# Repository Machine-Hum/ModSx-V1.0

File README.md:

ModSx-V1.0
==========

Please note this project has been discontined, see ModSx-V2.0.

https://github.com/Machine-Hum/ModSx-V2.0

The ModSx isa cross between the Arduino and a modular synths. 
Each module is a PCB that stacks on top of other modules. DC lines and signaling lines flow up 
the stack, these provide power, analog data and digital data to all the connected modules. Right 
angle headers are used for analog signal routing where needed. Wires are used to connect channels. 
The purpose is to reduce cost of modular synths by removing the mechanical aspect. Boards will use 
through hole components where possible, to enable the user to solder their own modules. The entire 
project will increase the accessibility of high quality audio components while increasing the 
customizability, yet keeping the complexity low to the end user.

PowerBoard
--------
/PowerBoard.JPG)

The power board, takes DC Vin from a large right angle screw terminal or power jack and conditions it to +3.3V, +5V, +0.5(Vin) and -0.5(Vin). Vin typical would be +24V, giving a +12V and -12V. 

AuxBreak
--------
/AuxBreak.JPG)

The Aux breakout, breaks out standard 3.5mm auxiliary cables into pins. The pins serve as interconnects for signal routing.

Proto Board
--------
/ProtoBoard.JPG)

The protoboard is for prototyping future circuits, basic hole patterns on the top for soldering.

8Bit LFO / VCO
--------
Low frequency oscillator (1-20Hz) sin, triangle or square wave. Takes in 0-10V into input pin, frequency is scaled linearly throughout the range. Waveform is selected from 0/10V discrete signal on pins.
Ideally the same board will be used for 2Khz-20Khz VCO, but I’m worried that the uC will not be able to keep up. VCO might be square wave only.

Power Amp
--------
/PowerAmp.JPG)

The power amp is a 4 channel low wattage amplifier based off the LM386. 

-Walker

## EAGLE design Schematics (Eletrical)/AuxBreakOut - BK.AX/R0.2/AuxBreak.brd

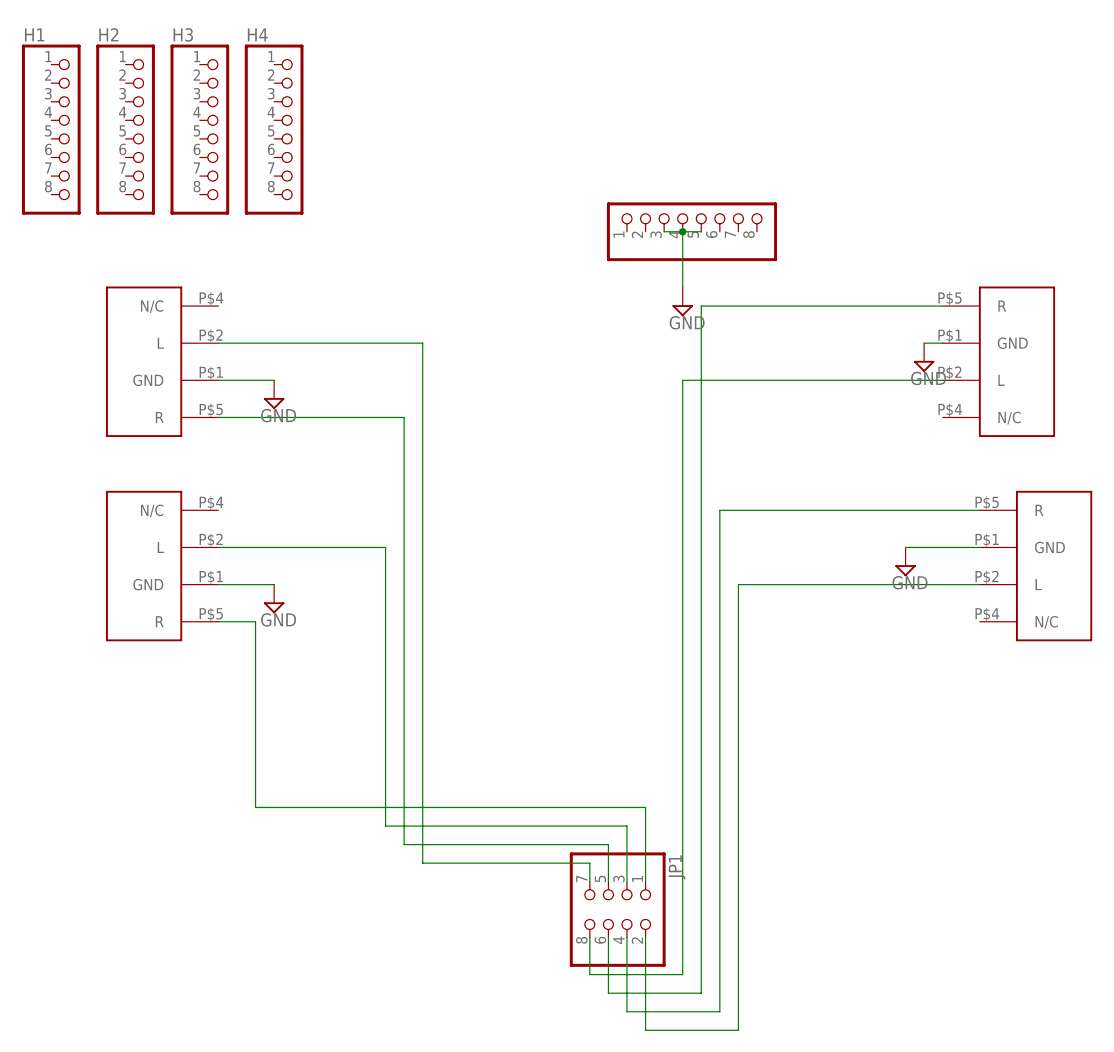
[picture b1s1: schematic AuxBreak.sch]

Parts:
H1, H2, H3, H4, H5: PINHD-1X8; 1X08
JP1: PINHD-2X4/90; 2X04/90
U$1, U$3, U$4, U$5: 161-3509-E

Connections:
GND: H5.3, H5.4, H5.5, U$1.P$1 (GND), U$3.P$1 (GND), U$4.P$1 (GND), U$5.P$1 (GND)
unnamed: JP1.7, U$5.P$2 (L)
unnamed: JP1.5, U$5.P$5 (R)
unnamed: JP1.3, U$4.P$2 (L)
unnamed: JP1.1, U$4.P$5 (R)
unnamed: JP1.8, U$1.P$2 (L)
unnamed: JP1.6, U$1.P$5 (R)
unnamed: JP1.4, U$3.P$5 (R)
unnamed: JP1.2, U$3.P$2 (L)

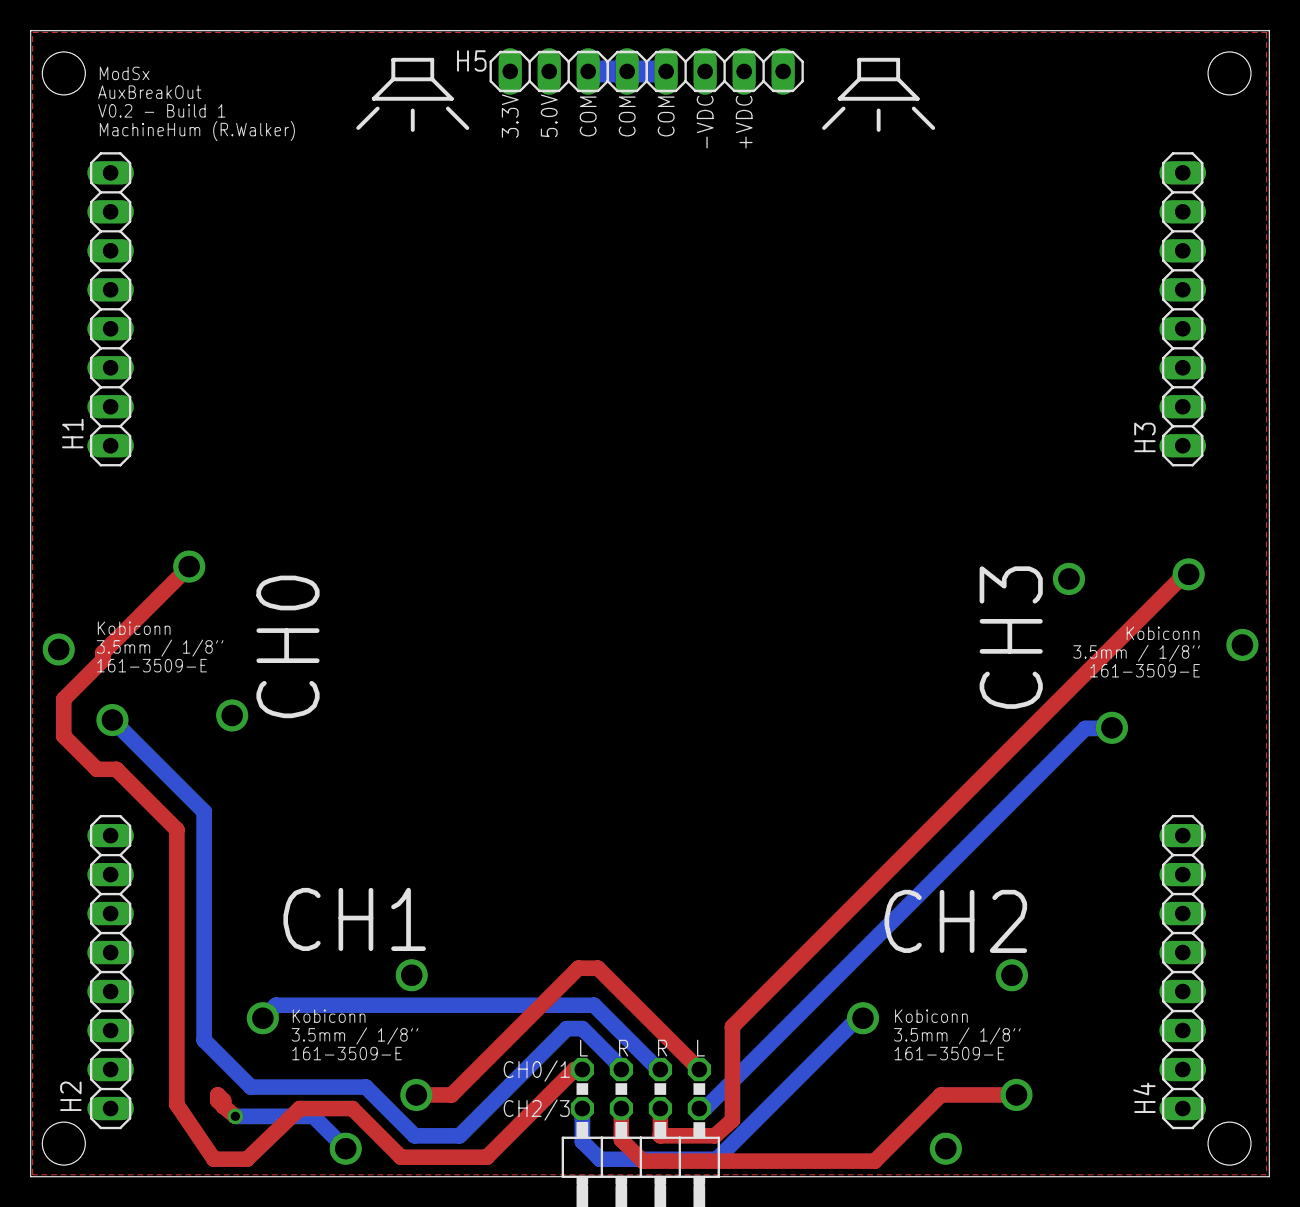
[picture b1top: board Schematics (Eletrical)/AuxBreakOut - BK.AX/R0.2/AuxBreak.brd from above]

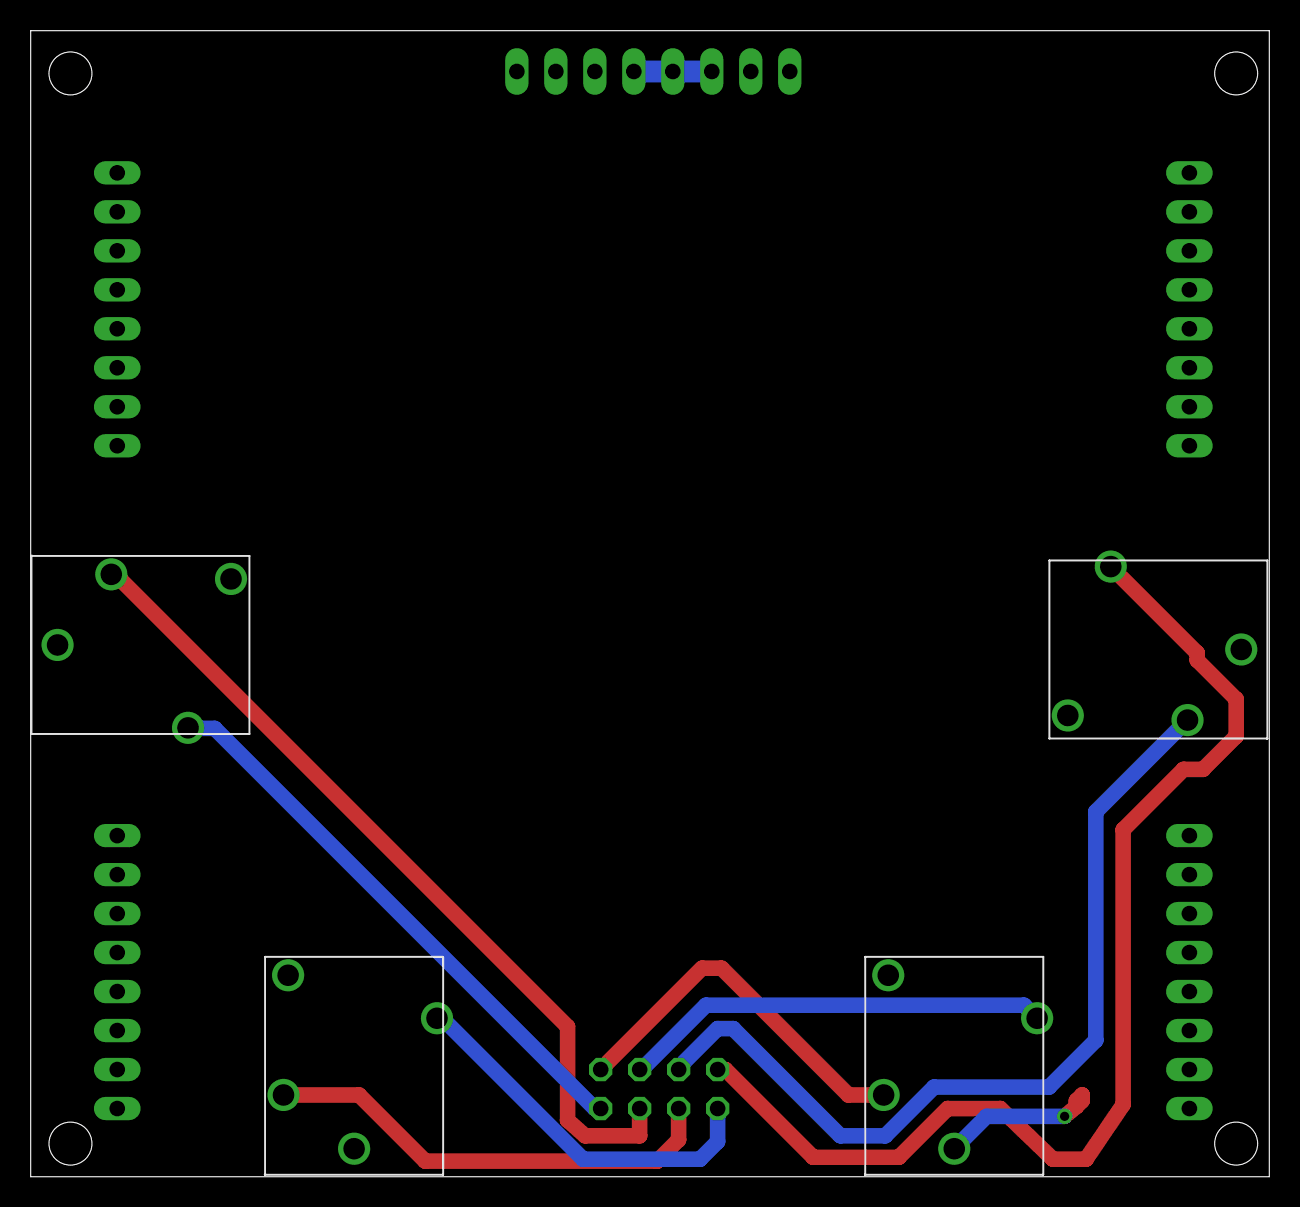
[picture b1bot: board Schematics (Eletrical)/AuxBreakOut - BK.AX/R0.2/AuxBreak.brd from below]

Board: 2 copper layers, 80.7 x 74.7 mm, 10 parts (4 on the bottom side), 9 nets.

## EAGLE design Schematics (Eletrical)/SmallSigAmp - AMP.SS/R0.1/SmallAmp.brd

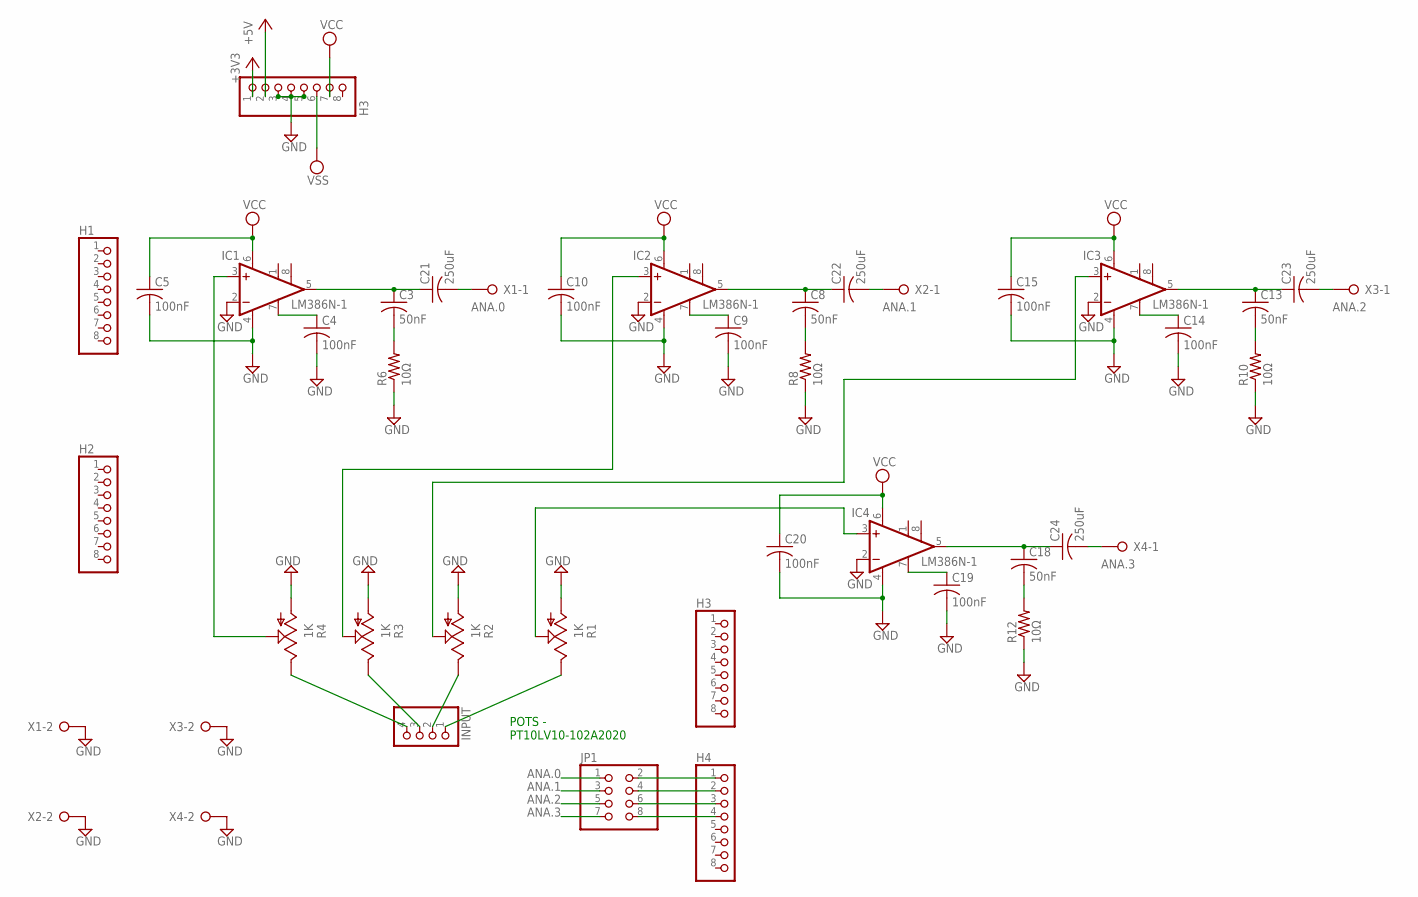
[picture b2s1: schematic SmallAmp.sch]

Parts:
C3, C8, C13, C18: 50nF; C075-032X103
C4, C5, C9, C10, C14, C15, C19, C20: 100nF; C075-032X103
C21, C22, C23, C24: 250uF; C025-050X050
H1, H2, H3, H4: PINHD-1X8; 1X08
IC1, IC2, IC3, IC4: LM386N-1; DIL08
INPUT: PINHD-1X4/90; 1X04/90
JP1: PINHD-2X4; 2X04
JP3: H3; 1X08
R1, R2, R3, R4: 1K; PT-10
R6, R8, R10, R12: 10Ω; 0204/7
X1, X2, X3, X4: W237-02P; W237-132

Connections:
+3V3: JP3.1
+5V: JP3.2
ANA.0: C21.2, JP1.1, X1.1
ANA.1: C22.2, JP1.3, X2.1
ANA.2: C23.2, JP1.5, X3.1
ANA.3: C24.2, JP1.7, X4.1
GND: C4.2, C5.2, C9.2, C10.2, C14.2, C15.2, C19.2, C20.2, IC1.2 (-IN), IC1.4 (GND), IC2.2 (-IN), IC2.4 (GND), IC3.2 (-IN), IC3.4 (GND), IC4.2 (-IN), IC4.4 (GND), JP3.3, JP3.4, JP3.5, R1.A, R2.A, R3.A, R4.A, R6.1, R8.1, R10.1, R12.1, X1.2, X2.2, X3.2, X4.2
unnamed: INPUT.1, R1.E
unnamed: INPUT.2, R2.E
unnamed: INPUT.3, R3.E
unnamed: INPUT.4, R4.E
unnamed: IC1.3 (+IN), R4.S
unnamed: H4.1, JP1.2
unnamed: C3.1, C21.1, IC1.5 (OUT)
unnamed: H4.2, JP1.4
unnamed: C3.2, R6.2
unnamed: C4.1, IC1.7 (BYPASS)
unnamed: IC2.3 (+IN), R3.S
unnamed: C8.1, C22.1, IC2.5 (OUT)
unnamed: H4.3, JP1.6
unnamed: C8.2, R8.2
unnamed: H4.4, JP1.8
unnamed: C9.1, IC2.7 (BYPASS)
unnamed: IC3.3 (+IN), R2.S
unnamed: C13.1, C23.1, IC3.5 (OUT)
unnamed: C13.2, R10.2
unnamed: C14.1, IC3.7 (BYPASS)
unnamed: IC4.3 (+IN), R1.S
unnamed: C18.1, C24.1, IC4.5 (OUT)
unnamed: C18.2, R12.2
unnamed: C19.1, IC4.7 (BYPASS)
VCC: C5.1, C10.1, C15.1, C20.1, IC1.6 (VS), IC2.6 (VS), IC3.6 (VS), IC4.6 (VS), JP3.7
VSS: JP3.6

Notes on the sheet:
POTS - PT10LV10-102A2020
ANA.0
ANA.1
ANA.2
ANA.3

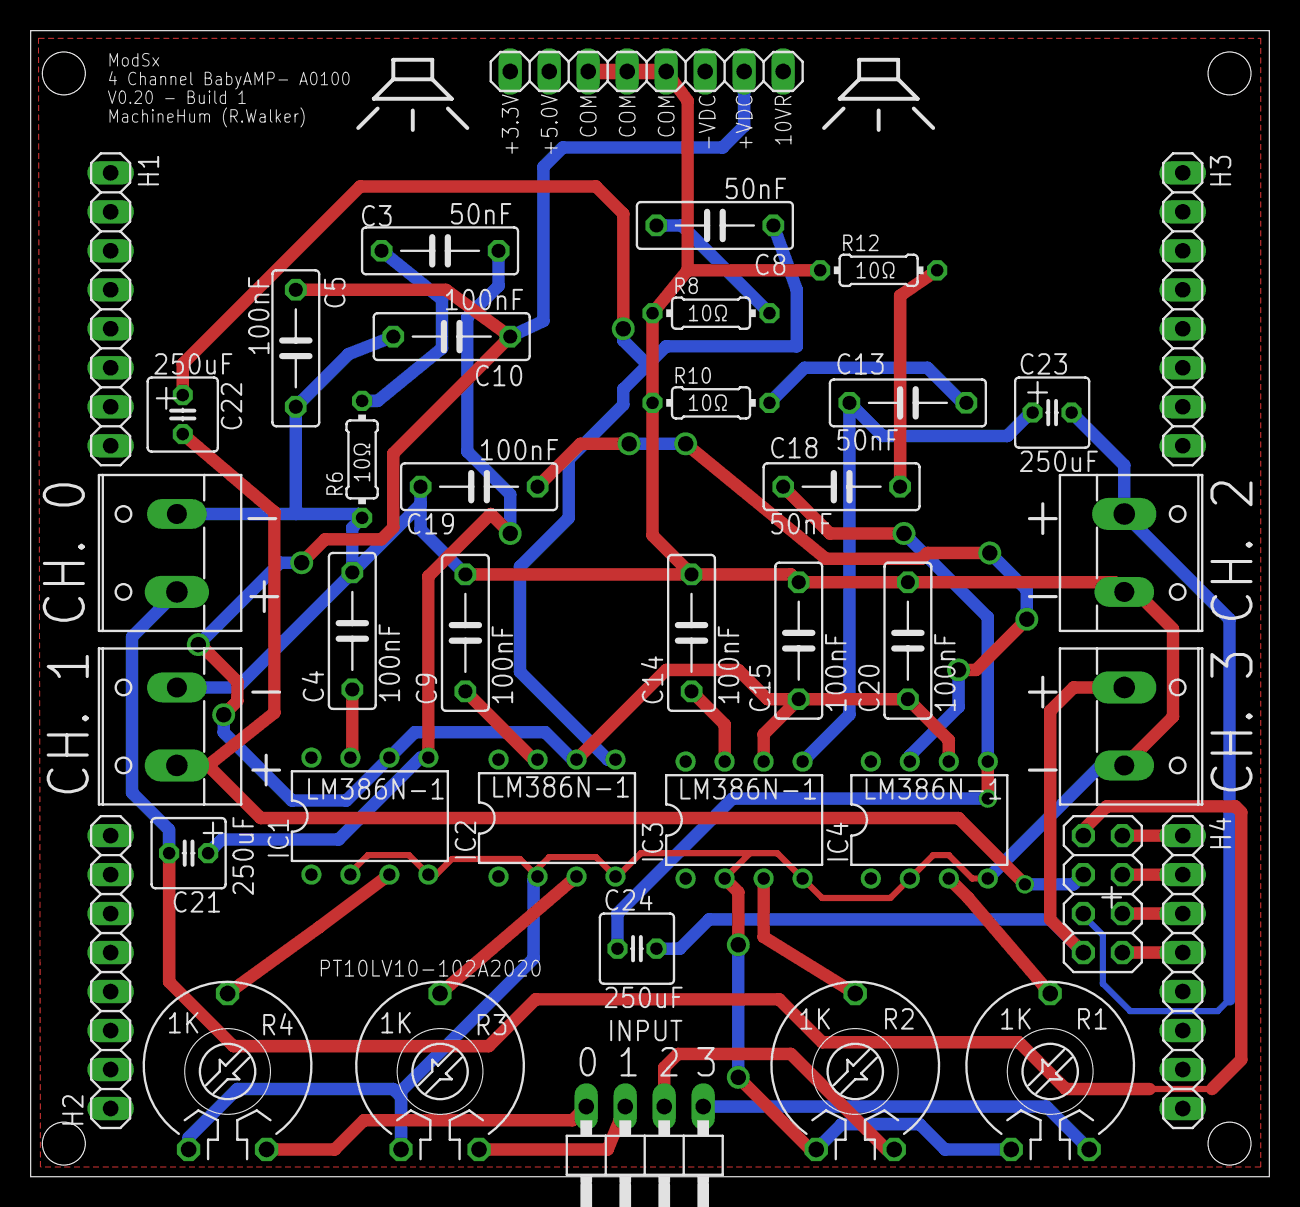
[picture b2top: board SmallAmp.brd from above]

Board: 2 copper layers, 80.7 x 74.7 mm, 39 parts (0 on the bottom side), 30 nets.

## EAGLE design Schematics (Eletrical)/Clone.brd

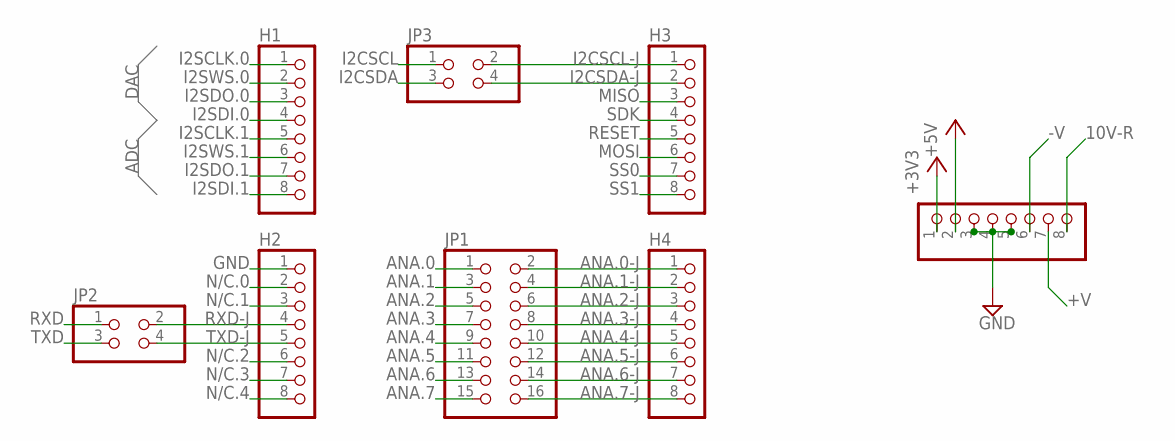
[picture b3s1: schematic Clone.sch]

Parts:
H1, H2, H3, H4, H5: PINHD-1X8; 1X08
JP1: PINHD-2X8; 2X08
JP2, JP3: PINHD-2X2; 2X02

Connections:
10V-R: H5.8
+3V3: H5.1
+5V: H5.2
+V: H5.7
-V: H5.6
ANA.0: JP1.1
ANA.0-J: H4.1, JP1.2
ANA.1: JP1.3
ANA.1-J: H4.2, JP1.4
ANA.2: JP1.5
ANA.2-J: H4.3, JP1.6
ANA.3: JP1.7
ANA.3-J: H4.4, JP1.8
ANA.4: JP1.9
ANA.4-J: H4.5, JP1.10
ANA.5: JP1.11
ANA.5-J: H4.6, JP1.12
ANA.6: JP1.13
ANA.6-J: H4.7, JP1.14
ANA.7: JP1.15
ANA.7-J: H4.8, JP1.16
GND: H2.1, H5.3, H5.4, H5.5
I2CSCL: JP3.1
I2CSCL-J: H3.1, JP3.2
I2CSDA: JP3.3
I2CSDA-J: H3.2, JP3.4
I2SCLK.0: H1.1
I2SCLK.1: H1.5
I2SDI.0: H1.4
I2SDI.1: H1.8
I2SDO.0: H1.3
I2SDO.1: H1.7
I2SWS.0: H1.2
I2SWS.1: H1.6
MISO: H3.3
MOSI: H3.6
N/C.0: H2.2
N/C.1: H2.3
N/C.2: H2.6
N/C.3: H2.7
N/C.4: H2.8
RESET: H3.5
RXD: JP2.1
RXD-J: H2.4, JP2.2
SCK: H3.4
SS0: H3.7
SS1: H3.8
TXD: JP2.3
TXD-J: H2.5, JP2.4

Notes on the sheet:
10V-R
I2SCLK.0
I2SWS.0
I2SDO.0
I2SDI.0
I2SCLK.1
I2SWS.1
I2SDO.1
I2SDI.1
GND
N/C.0
RXD-J
TXD-J
N/C.1
N/C.2
N/C.3
N/C.4
I2CSCL
I2CSDA
MISO
SDK
RESET
MOSI
SS0
SS1
ANA.0-J
ANA.1-J
ANA.2-J
ANA.3-J
ANA.4-J
ANA.5-J
ANA.6-J
ANA.7-J
ANA.0
ANA.1
ANA.2
ANA.3
ANA.4
ANA.5
ANA.6

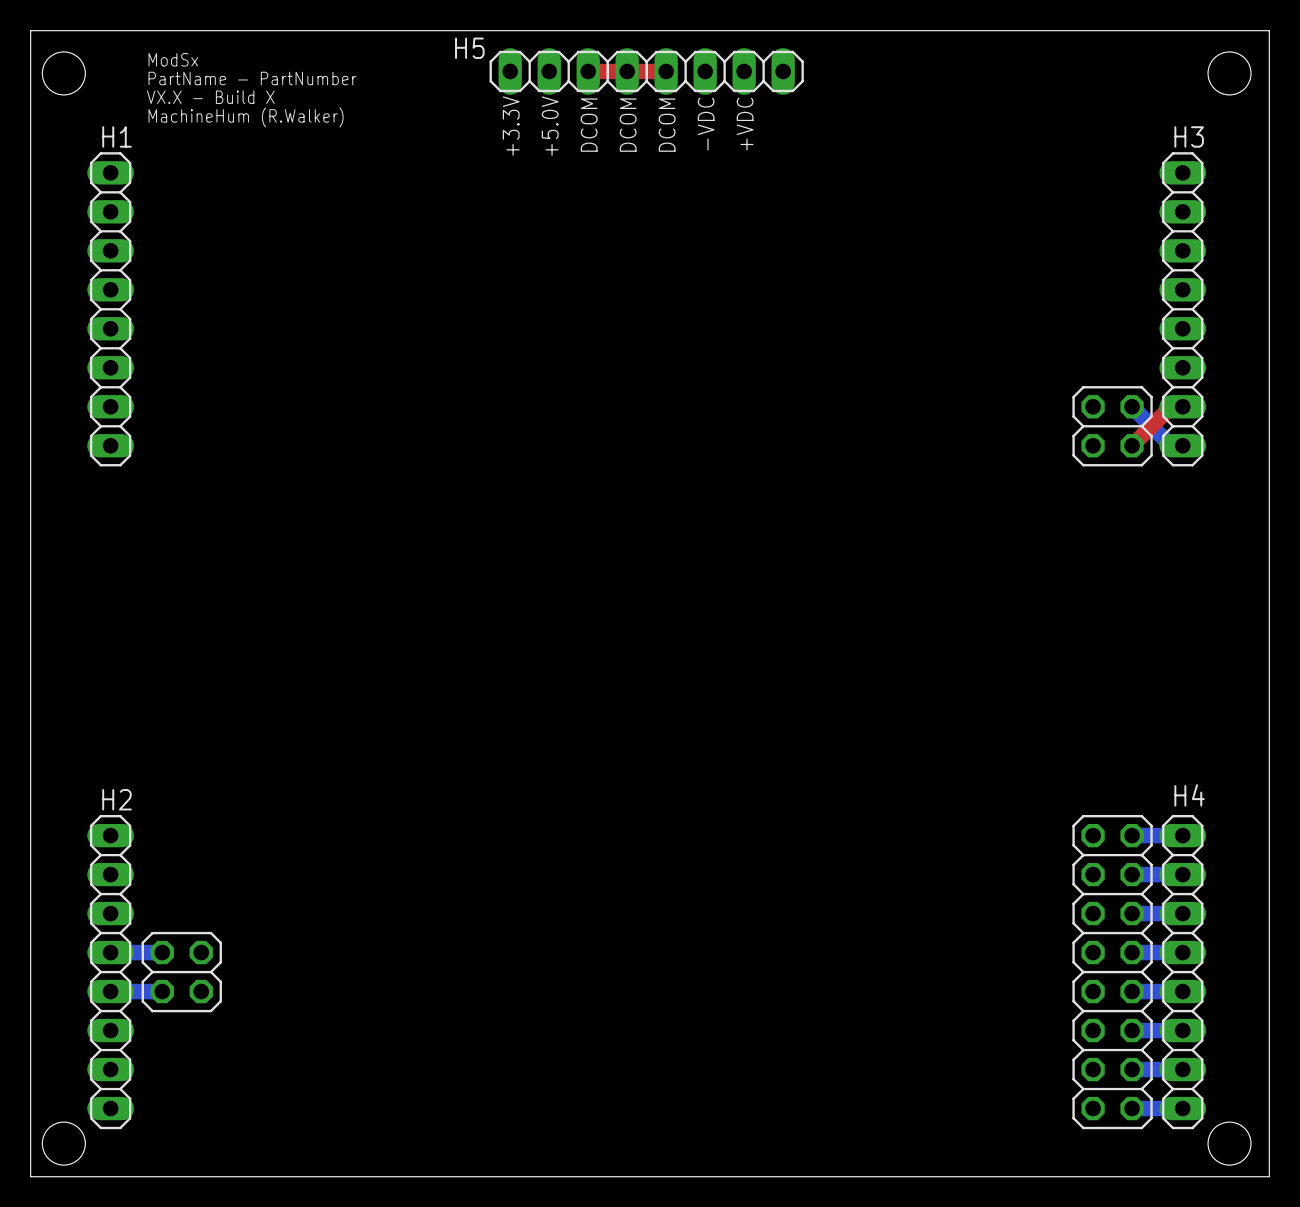
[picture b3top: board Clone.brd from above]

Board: 2 copper layers, 80.7 x 74.7 mm, 8 parts (0 on the bottom side), 13 nets.

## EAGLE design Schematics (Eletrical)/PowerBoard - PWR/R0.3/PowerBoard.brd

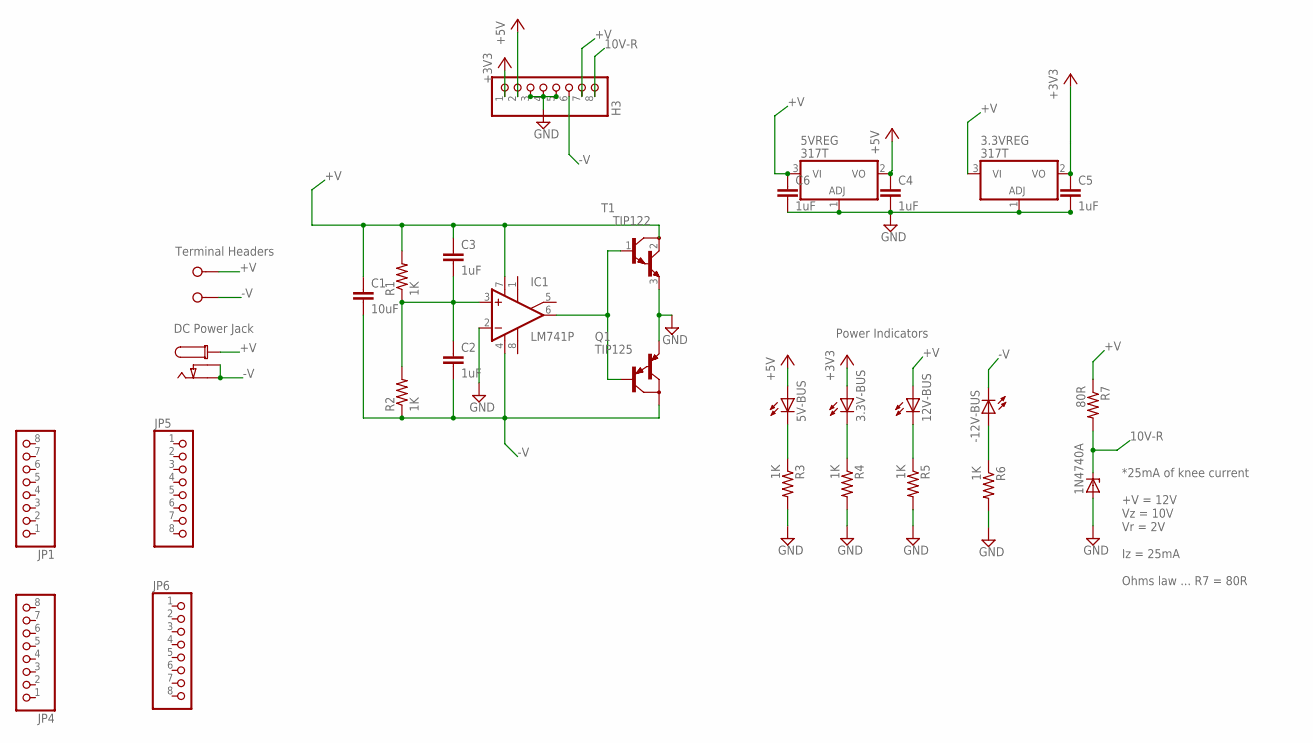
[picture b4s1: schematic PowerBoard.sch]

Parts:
1N4740A: ZENER-DIODEDO34-7; DO34Z7
3.3V-BUS, 5V-BUS, 12V-BUS: LED-5MM
3.3VREG, 5VREG: 317T; TO220H
-12V-BUS: LED-5MM
C1: 10uF; C2.5-2
C2, C3, C4, C5, C6: 1uF; C2.5-2
IC1: LM741P; DIL08
J1: CON_DC_M-DC_PTH; DC_BARREL_JACK_PTH_2MM
JP1, JP4, JP5, JP6: PINHD-1X8; 1X08
JP3: H3; 1X08
Q1: TIP125; TO220
R1, R2, R3, R4, R5, R6: 1K; 0207/7
R7: 80R; 0207/7
T1: TIP122; TO220
X1: W237-02P; W237-132

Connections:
10V-R: 1N4740A.C, JP3.8, R7.2
+3V3: 3.3V-BUS.A, 3.3VREG.2 (VO), C5.1, JP3.1
+5V: 5V-BUS.A, 5VREG.2 (VO), C4.1, JP3.2
+V: 3.3VREG.3 (VI), 5VREG.3 (VI), 12V-BUS.A, C1.1, C3.1, C6.1, IC1.7 (V+), J1.P1, JP3.7, R1.2, R7.1, T1.2 (C), X1.2
-V: -12V-BUS.K (C), C1.2, C2.2, IC1.4 (V-), J1.P2 (P3), J1.P3 (P2), JP3.6, Q1.2 (C), R2.1, X1.1
GND: 1N4740A.A, 3.3VREG.1 (ADJ), 5VREG.1 (ADJ), C4.2, C5.2, C6.2, IC1.2 (-IN), JP3.3, JP3.4, JP3.5, Q1.3 (E), R3.2, R4.2, R5.2, R6.2, T1.3 (E)
unnamed: 5V-BUS.K (C), R3.1
unnamed: 3.3V-BUS.K (C), R4.1
unnamed: 12V-BUS.K (C), R5.1
unnamed: -12V-BUS.A, R6.1
unnamed: IC1.6 (OUT), Q1.1 (B), T1.1 (B)
unnamed: C2.1, C3.2, IC1.3 (+IN), R1.1, R2.2

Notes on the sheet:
DC Power Jack
Terminal Headers
Power Indicators
10V-R
*25mA of knee current +V = 12V Vz = 10V Vr = 2V Iz = 25mA Ohms law ... R7 = 80R

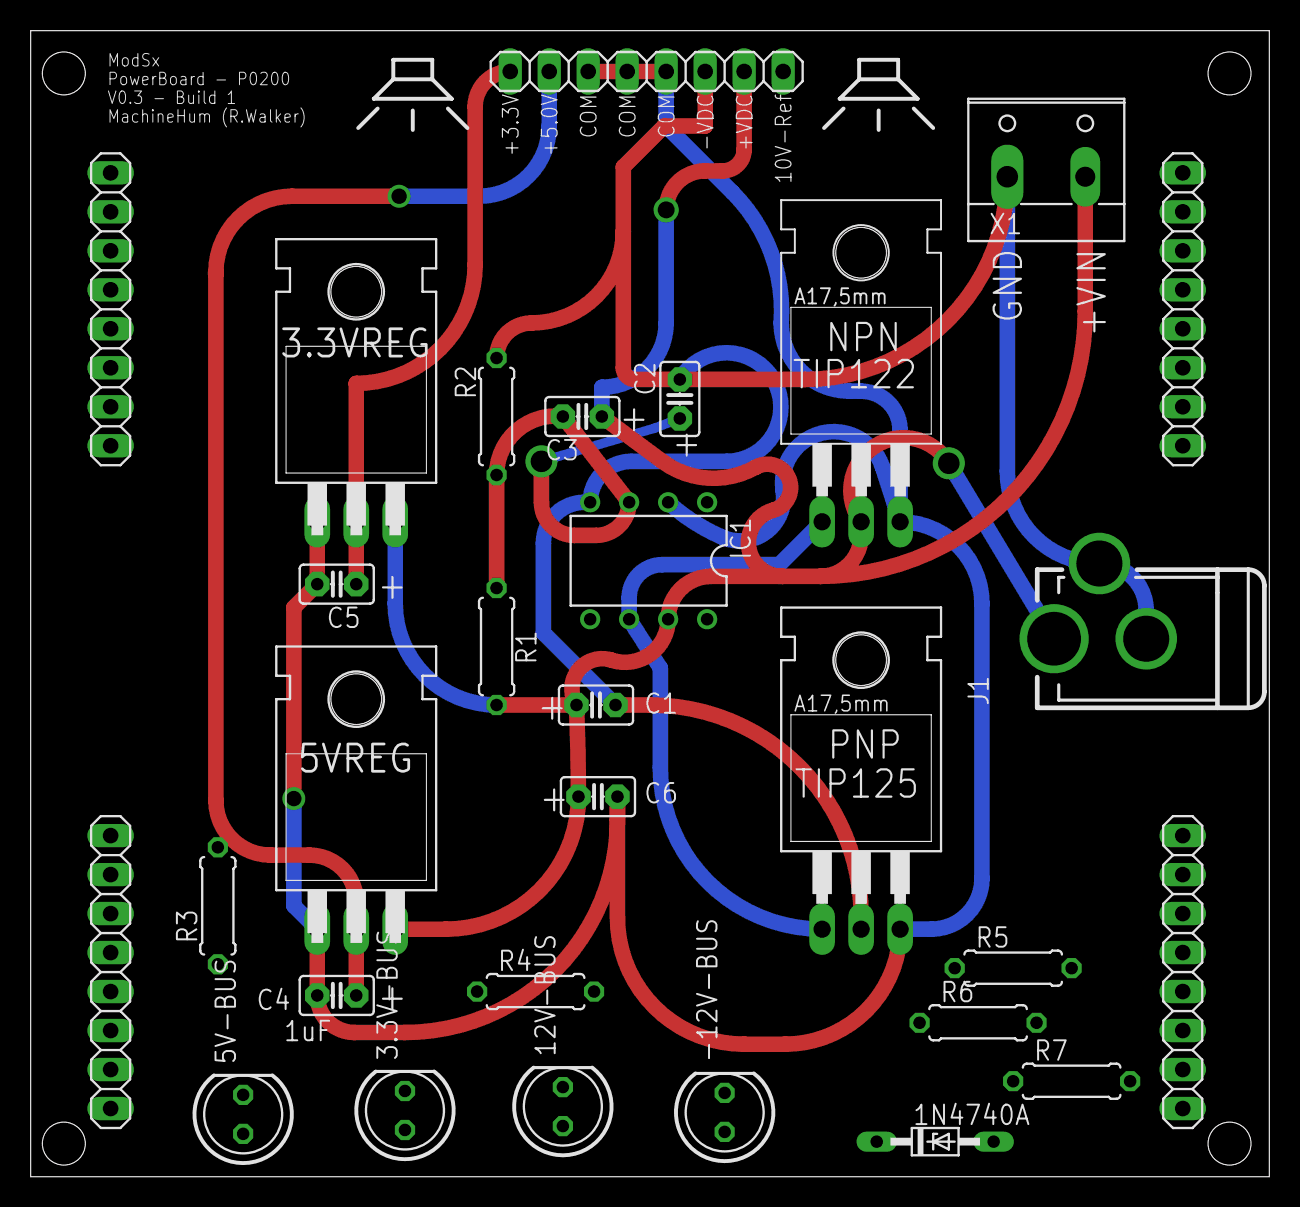
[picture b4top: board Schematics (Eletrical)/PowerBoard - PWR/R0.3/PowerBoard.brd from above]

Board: 2 copper layers, 80.7 x 74.7 mm, 30 parts (0 on the bottom side), 12 nets.

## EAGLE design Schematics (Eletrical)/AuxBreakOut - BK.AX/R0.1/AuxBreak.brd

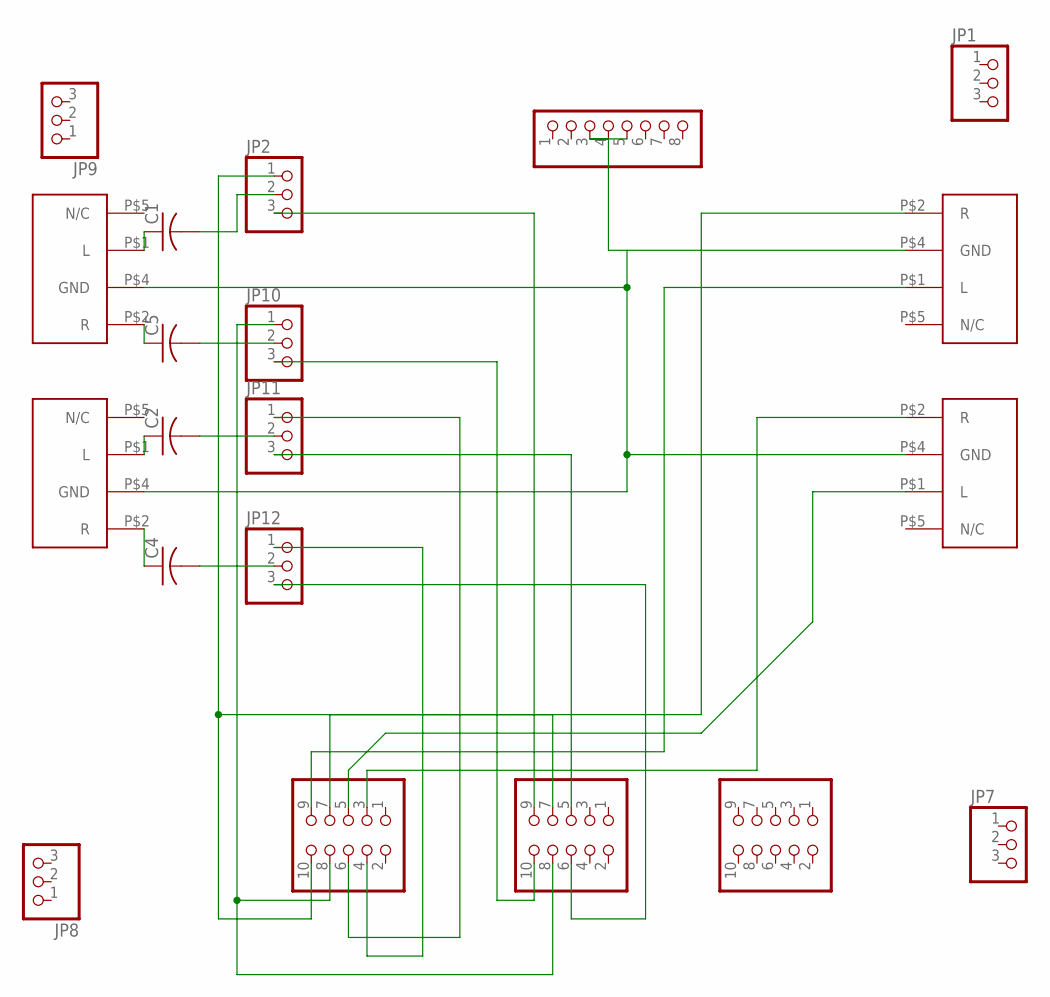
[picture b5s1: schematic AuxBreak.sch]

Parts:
C1, C2, C4, C5: C-US025-025X050; C025-025X050
JP1, JP2, JP7, JP8, JP9, JP10, JP11, JP12: PINHD-1X3; 1X03
JP3: PINHD-1X8; 1X08
JP4, JP5, JP6: PINHD-2X5/90; 2X05/90
U$1, U$3, U$4, U$5: 161-3509-E

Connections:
unnamed: JP3.3, JP3.4, JP3.5, U$1.P$4 (GND), U$3.P$4 (GND), U$4.P$4 (GND), U$5.P$4 (GND)
unnamed: C2.1, U$4.P$1 (L)
unnamed: C4.1, U$4.P$2 (R)
unnamed: C1.2, JP2.2
unnamed: C5.1, U$5.P$2 (R)
unnamed: JP2.1, JP4.7, JP6.10
unnamed: JP4.8, JP6.8, JP10.1
unnamed: JP6.6, JP11.1
unnamed: JP6.4, JP12.1
unnamed: C4.2, JP12.2
unnamed: C2.2, JP11.2
unnamed: C1.1, U$5.P$1 (L)
unnamed: C5.2, JP10.2
unnamed: JP2.3, JP4.9
unnamed: JP4.5, JP11.3
unnamed: JP4.10, JP10.3
unnamed: JP4.6, JP12.3
unnamed: JP6.9, U$3.P$1 (L)
unnamed: JP6.7, U$3.P$2 (R)
unnamed: JP6.5, U$1.P$1 (L)
unnamed: JP6.3, U$1.P$2 (R)

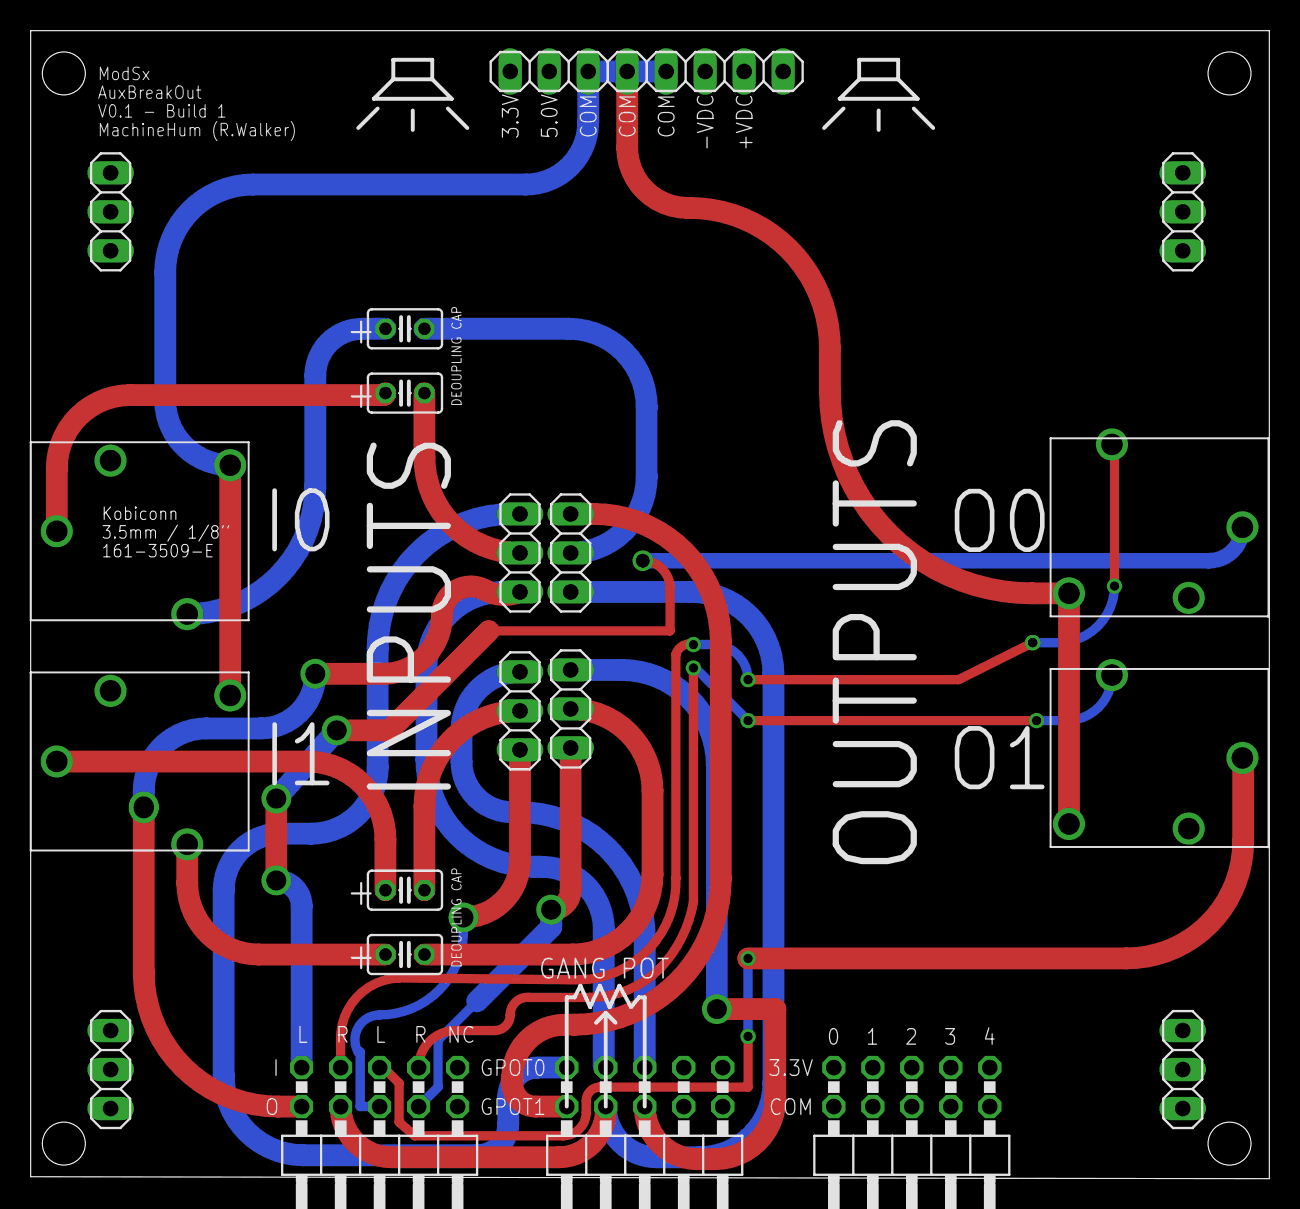
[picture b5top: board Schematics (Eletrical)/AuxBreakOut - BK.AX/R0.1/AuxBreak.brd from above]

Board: 2 copper layers, 80.7 x 74.8 mm, 20 parts (0 on the bottom side), 21 nets.

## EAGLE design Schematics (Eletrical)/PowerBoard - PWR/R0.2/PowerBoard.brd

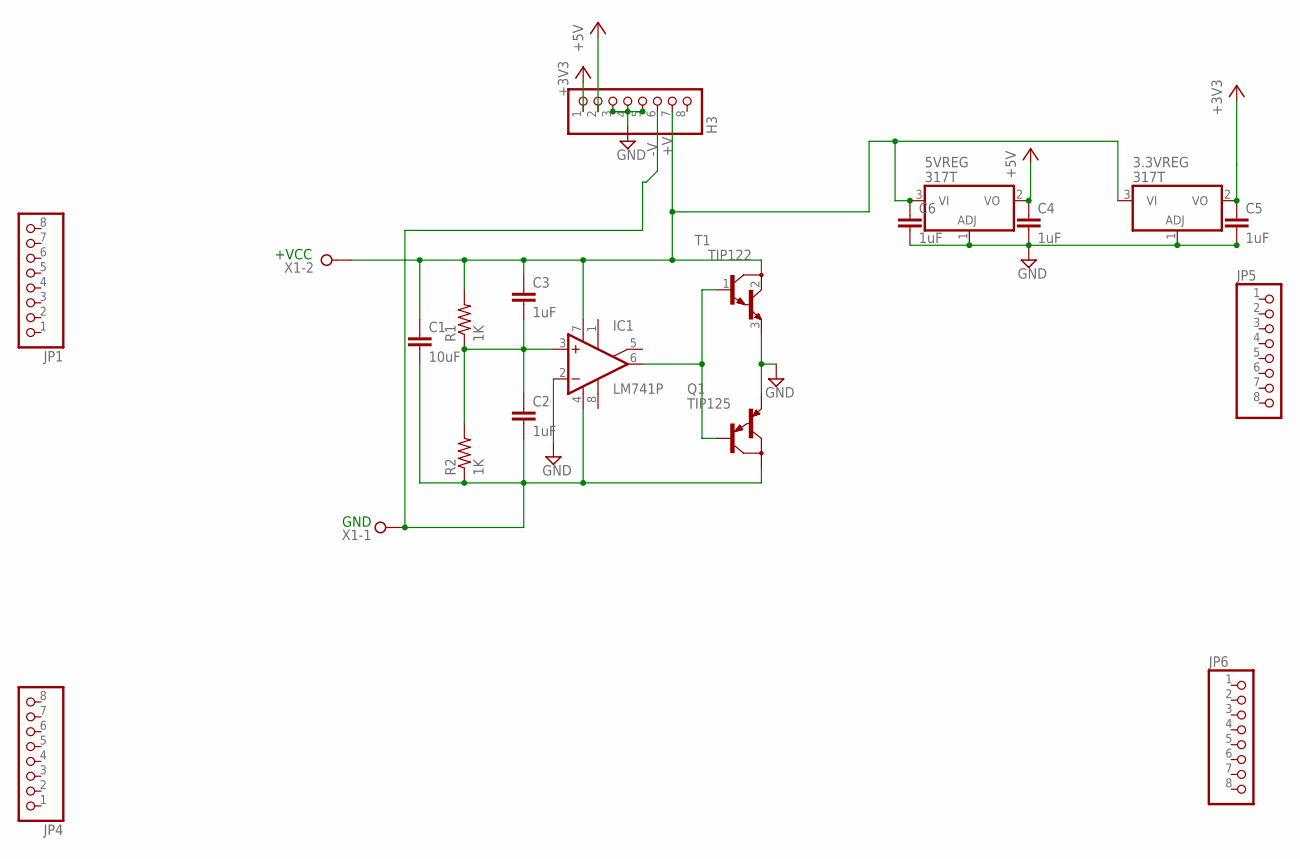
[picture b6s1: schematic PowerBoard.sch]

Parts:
3.3VREG, 5VREG: 317T; TO220H
C1: 10uF; C2.5-2
C2, C3, C4, C5, C6: 1uF; C2.5-2
IC1: LM741P; DIL08
JP1, JP4, JP5, JP6: PINHD-1X8; 1X08
JP3: H3; 1X08
Q1: TIP125; TO220
R1, R2: 1K; 0207/7
T1: TIP122; TO220
X1: W237-02P; W237-132

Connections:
+3V3: 3.3VREG.2 (VO), C5.1, JP3.1
+5V: 5VREG.2 (VO), C4.1, JP3.2
GND: 3.3VREG.1 (ADJ), 5VREG.1 (ADJ), C4.2, C5.2, C6.2, IC1.2 (-IN), JP3.3, JP3.4, JP3.5, Q1.3 (E), T1.3 (E)
unnamed: C1.2, C2.2, IC1.4 (V-), JP3.6, Q1.2 (C), R2.1, X1.1
unnamed: 3.3VREG.3 (VI), 5VREG.3 (VI), C1.1, C3.1, C6.1, IC1.7 (V+), JP3.7, R1.2, T1.2 (C), X1.2
unnamed: IC1.6 (OUT), Q1.1 (B), T1.1 (B)
unnamed: C2.1, C3.2, IC1.3 (+IN), R1.1, R2.2

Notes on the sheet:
+VCC
GND

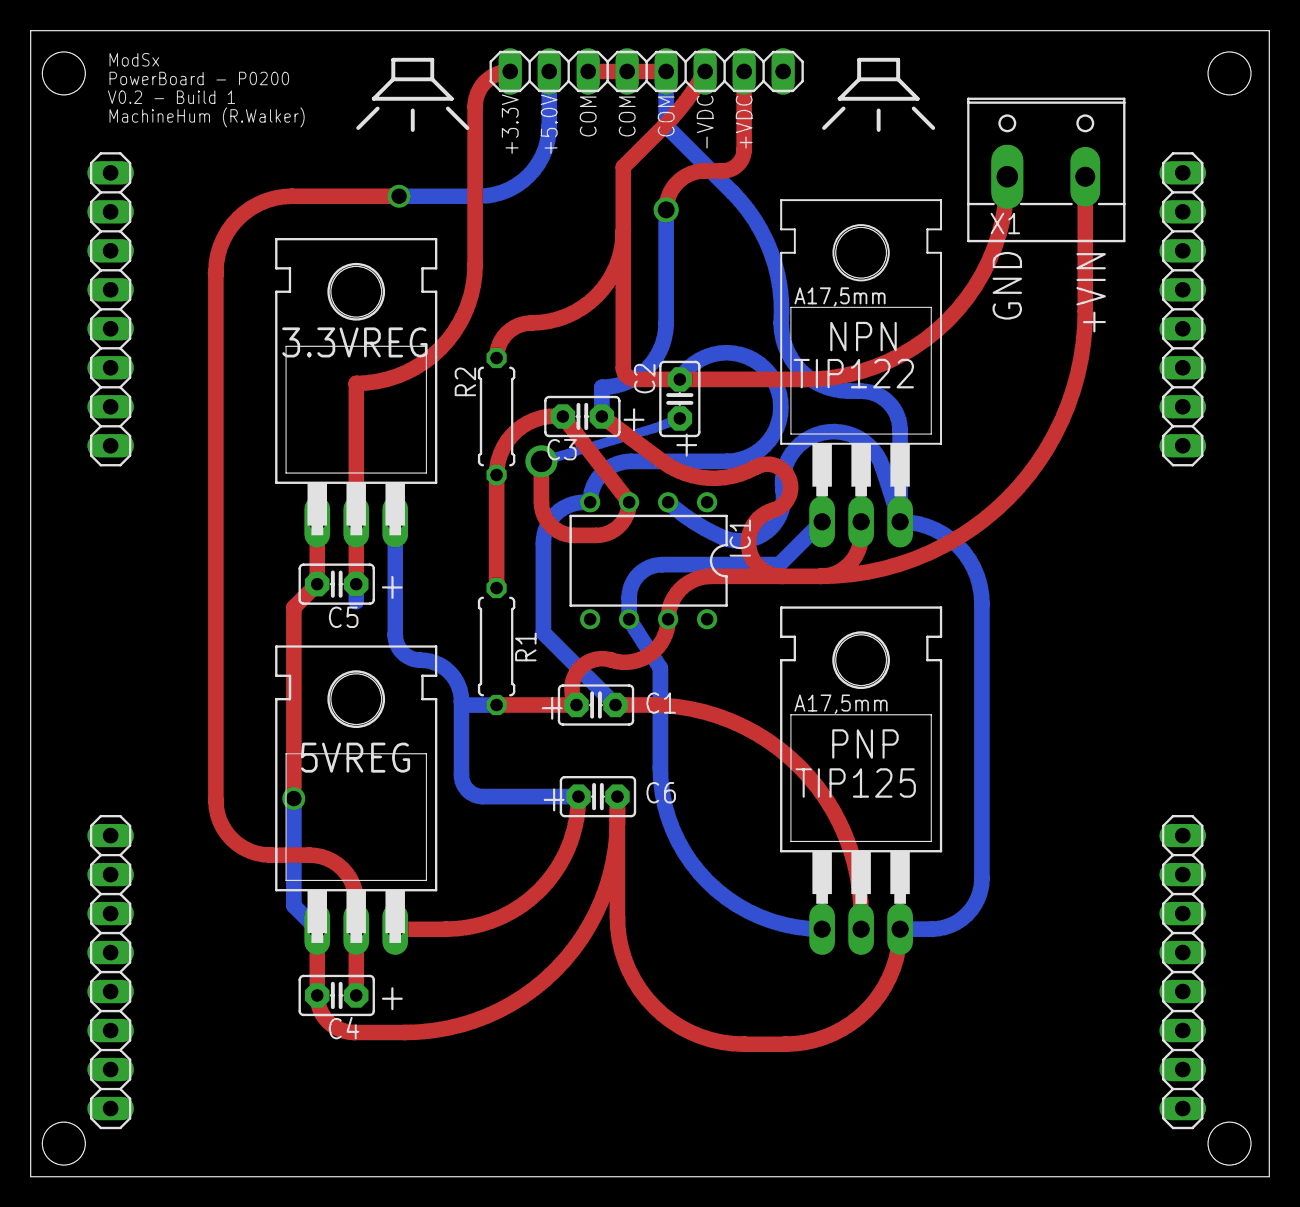
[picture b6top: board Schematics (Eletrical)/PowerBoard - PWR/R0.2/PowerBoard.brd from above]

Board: 2 copper layers, 80.7 x 74.7 mm, 19 parts (0 on the bottom side), 7 nets.
